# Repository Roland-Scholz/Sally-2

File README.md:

# Sally-2

An ATR8000 (https://www.atarimagazines.com/v3n4/ATR8000.php, http://atariki.krap.pl/index.php/ATR_8000) clone formerly made by SWP
and the Sally 1 by RSD (Rainer Storz Datentechnik)

Inspired by the repair of a Sally 1, which had been found in the attic, the
Atari-Bit-Byter-User-Club (www.abbuc.de) encouraged Marc and me to reproduce this lovely machine in a more compact way, 
though keeping a sort of retro-style.

We used 3 16V8 GALs in order to reduce chip count and replaced the WD1797 floppy-disc-controller by the more compact
WD1772 variant. Caveat: This chip is not designed for HD (500kbit/s) speed used by 3 1/2" and 8"-drives, although most 
can be overclocked to that speed. Only use WD1772PH-02-02 version and at your own risk.
If you can get hold on an AJAX chip used in e.g. ATARI STE, use this one as it is rated for HD and even ED speed (16/32 Mhz).

Build your own device: All required files, components and documentations can be found in the release drawer 
https://github.com/Roland-Scholz/Sally-2/tree/main/release

You also could become an ABBUC member and buy a DIY kit at https://www.abbuc.de
Join the illustrous community and take part in conventions and discussions.

After some testing and debugging, the vRetro VR177x FDC replacement can now be recommended for use with this interface.
See https://www.vretrodesign.com/products/vr177x-wd1770-wd172-vl1772-replacement

# Key features:

- Operates either as standalone CP/M system or versatile ATARI 8-bit interface (up to 4 floppies, Centronics, RS232)
- Z80-CPU at 4Mhz
- 128k static RAM (64k usable)
- 8k EPROM, use any 8 / 16 / 32 / 64k device (burn sally2.hex at $8000)
- WD1772 FDC (or AJAX FDC or VR177x)
- Z80-CTC timer/counter

Additionally we have added:

- 57600 (actually 55.930) baud high speed SIO (Pokey divisor 9, drive responds to the "Get Speed Byte" command '?')
- Track buffer

# Improvements as of November 2026

- Nearly the entire SIO intererface and disk access logic has been rewritten

- Adheres to ATARI SIO standards

- Disk log-in and media-analysis faster and much improved

- More formats, inclusive XF551 track/sector sequence. More or less any valid Percom config is possible

## Typical formats:

| Name | KB    | Sides | Tracks | Sectors | Bytes/Sec | Encoding | Freq      |
| ---- | ----- | ----- | ------ | ------- | --------- | -------- | --------- |
| SD   | 90    | 1     | 40     | 18      | 128       | FM       | 250kbit/s |
| MD   | 130   | 1     | 40     | 26      | 128       | MFM      | 250kbit/s |
| DD1  | 180   | 1     | 40     | 18      | 256       | MFM      | 250kbit/s |
| DD2  | 360   | 1     | 80     | 18      | 256       | MFM      | 250kbit/s |
| DD3  | 360   | 2     | 40     | 18      | 256       | MFM      | 250kbit/s |
| DD4  | 720   | 2     | 80     | 18      | 256       | MFM      | 250kbit/s |
| HD1  | 500,5 | 2     | 77     | 26      | 128       | FM       | 500kbit/s |
| HD2  | 1001  | 2     | 77     | 26      | 256       | MFM      | 500kbit/s |
| HD3  | 1440  | 2     | 80     | 36      | 256       | MFM      | 500kbit/s |
| HD4  | 1440  | 2     | 80     | 18      | 512       | MFM      | 500kbit/s |

# Final product ready as of October 2025

# further progress as of April 2025:

- Marc has completed a new manually routed PCB and 3 supporting PCBs for swicthes and connectors
- ATARI can read/write 3 1/2 HD disks formtted like 8"-disks (26sec x 77 trks x 2 sides = ca. 1MB)
  The challange was to allow for HD even for 300 rpm drives, instead of 360rom used by 8" and 5 1/4" drives.
- A full blown FAT-12 DOS for the ATARI is close to be finished, some more testing and minor additional features required/appreciated
- ABBUC now owns a Bumbu X1-carbon 3D printer, which has immediately been used to dress Sally-2 appropirately.

First try, all-in-one print, label and case

# first attempts

Original Sally 1 repaired (5 ICs were out of order) and tested with a 40Trk single sides drive.

First version of Sally 2 PCB and a case

ATR8000 CP/M running on Sally 1 (todo: Add picture of the Sally CP/M version, which is apart from the messages identical to the ATR8000)

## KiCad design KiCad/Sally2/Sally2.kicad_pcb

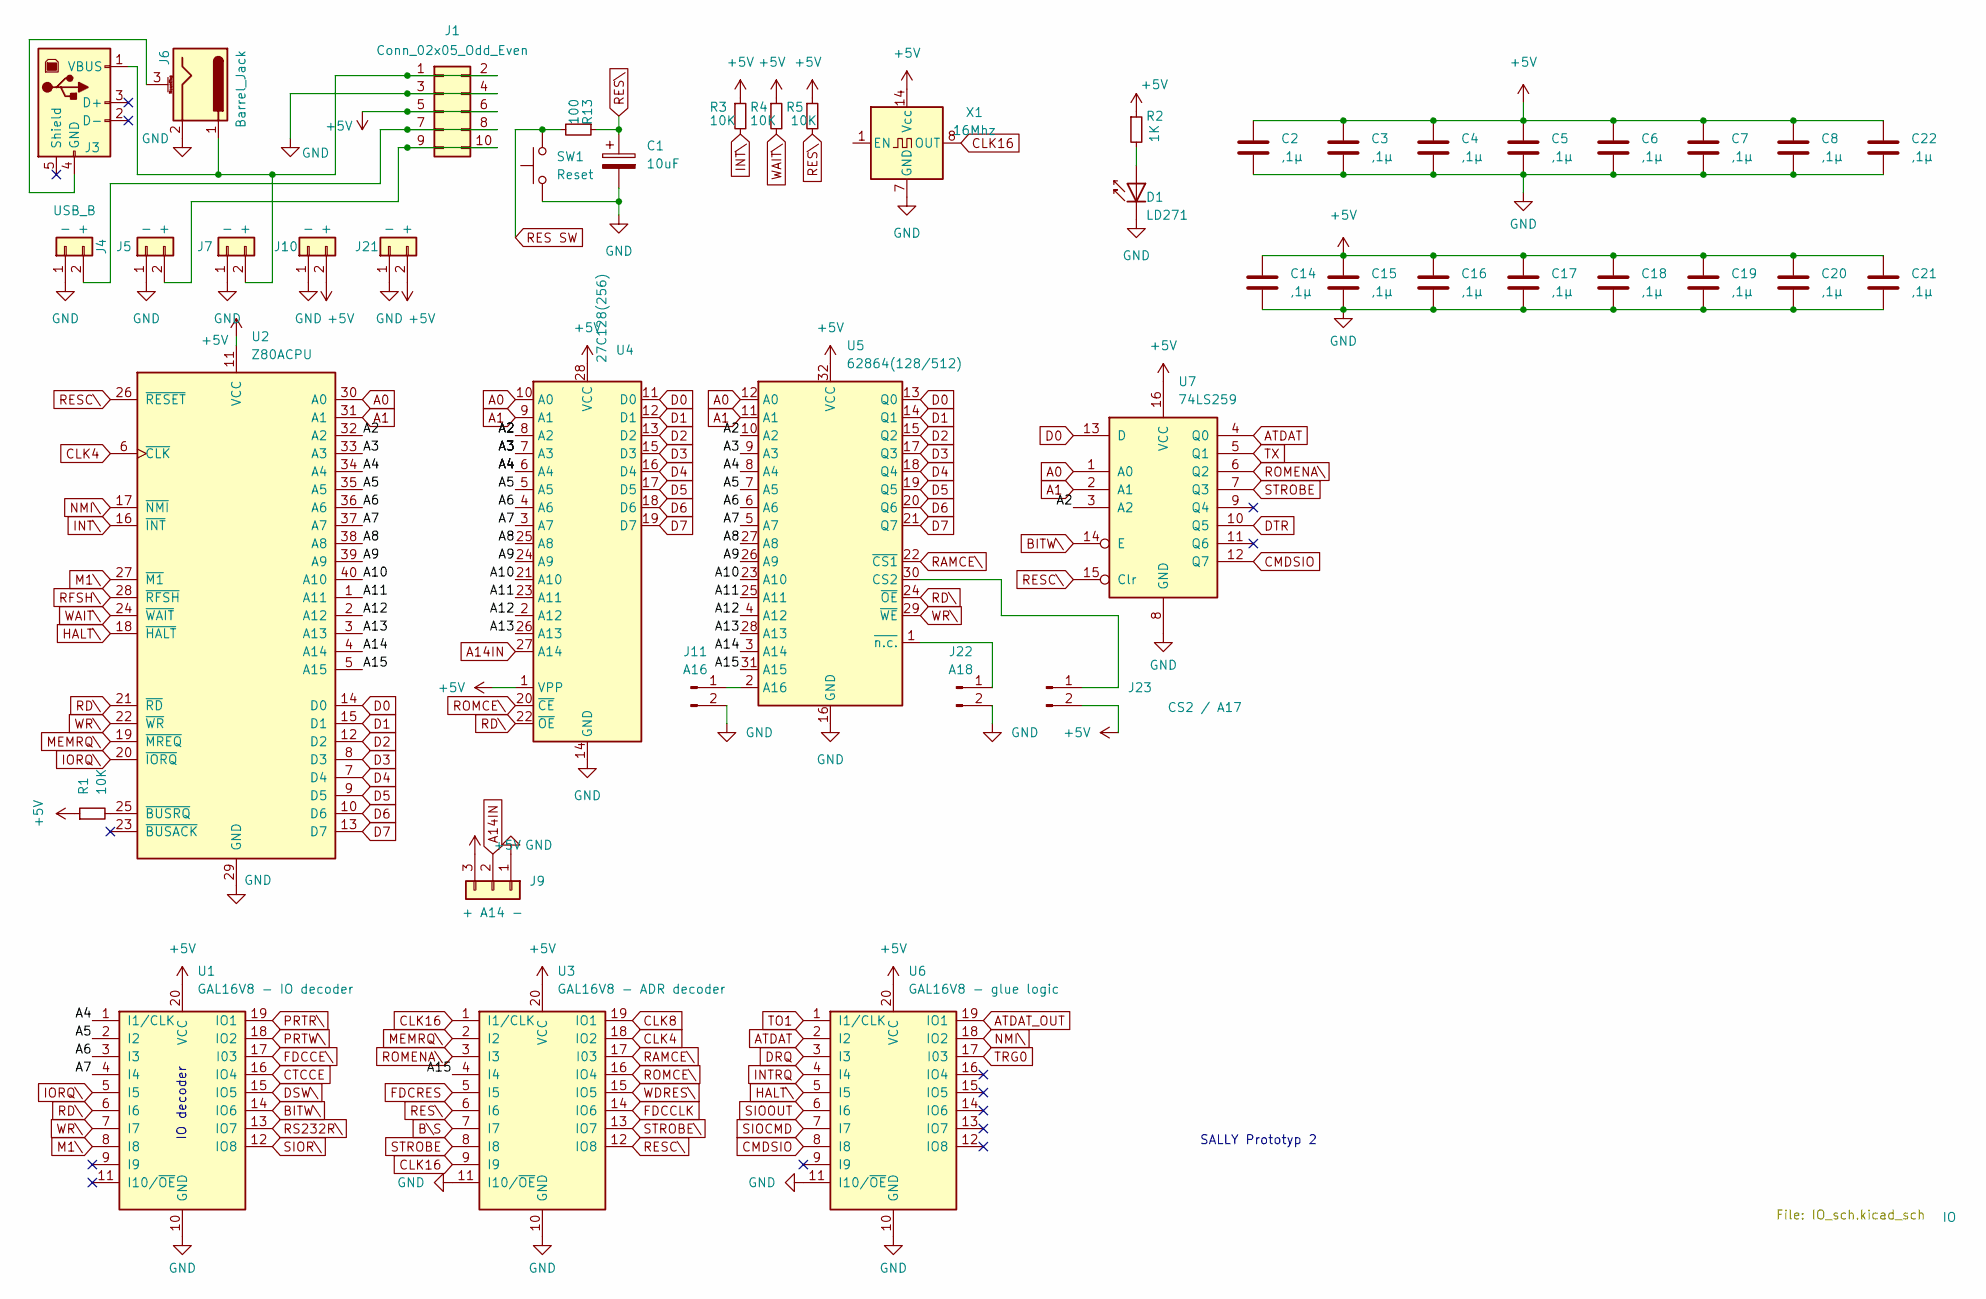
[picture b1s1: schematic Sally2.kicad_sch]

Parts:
C1: 10uF; CP_Radial_D5.0mm_P2.50mm
C2, C3, C4, C5, C6, C7, C8, C14, C15, C16, C17, C18, C19, C20, C21, C22: ,1µ; C_Disc_D5.0mm_W2.5mm_P5.00mm
D1: LD271; LED_D5.0mm_IRGrey
J1: Conn_02x05_Odd_Even; PinHeader_2x05_P2.54mm_Horizontal
J3: USB_B; USB_B_Lumberg_2411_02_Horizontal
J4, J5, J7, J10, J21: - +; BKL_1x2 72510U_P2.5mm_Vertical
J6: Barrel_Jack; BarrelJack_Horizontal
J9: + A14 -; PinHeader_1x03_P2.54mm_Vertical
J11: A16; PinHeader_1x02_P2.54mm_Vertical
J22: A18; PinHeader_1x02_P2.54mm_Vertical
J23: CS2 / A17; PinHeader_1x02_P2.54mm_Vertical
R1, R3, R4, R5: 10K; R_Axial_DIN0207_L6.3mm_D2.5mm_P10.16mm_Horizontal
R2: 1K; R_Axial_DIN0207_L6.3mm_D2.5mm_P10.16mm_Horizontal
R13: 100; R_Axial_DIN0207_L6.3mm_D2.5mm_P10.16mm_Horizontal
SW1: Reset; C_Rect_L7.5mm_W6.5mm_P5.00mm
U1: GAL16V8 - IO decoder; DIP-20_W7.62mm
U2: Z80ACPU; DIP-40_W15.24mm
U3: GAL16V8 - ADR decoder; DIP-20_W7.62mm
U4: 27C128(256); DIP-28_W15.24mm
U5: 62864(128/512); DIP-32_W15.24mm_Socket
U6: GAL16V8 - glue logic; DIP-20_W7.62mm
U7: 74LS259; DIP-16_W7.62mm
X1: 16Mhz; Oscillator_DIP-14

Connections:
+5V: C2.1, C3.1, C4.1, C5.1, C6.1, C7.1, C8.1, C14.1, C15.1, C16.1, C17.1, C18.1, C19.1, C20.1, C21.1, C22.1, J1.5, J1.6, J9.3, J10.2, J21.2, J23.2, R1.1, R2.1, R3.1, R4.1, R5.1, U1.20 (VCC), U2.11 (VCC), U3.20 (VCC), U4.1 (VPP), U4.28 (VCC), U5.32 (VCC), U6.20 (VCC), U7.16 (VCC), X1.14 (Vcc); also elsewhere on the board
/A2: U2.32 (A2), U4.8 (A2), U5.10 (A2), U7.3 (A2)
/A3: U2.33 (A3), U4.7 (A3), U5.9 (A3)
/A4: U1.1 (I1/CLK), U2.34 (A4), U4.6 (A4), U5.8 (A4)
/A5: U1.2 (I2), U2.35 (A5), U4.5 (A5), U5.7 (A5)
/A6: U1.3 (I3), U2.36 (A6), U4.4 (A6), U5.6 (A6)
/A7: U1.4 (I4), U2.37 (A7), U4.3 (A7), U5.5 (A7)
/A8: U2.38 (A8), U4.25 (A8), U5.27 (A8)
/A9: U2.39 (A9), U4.24 (A9), U5.26 (A9)
/A10: U2.40 (A10), U4.21 (A10), U5.23 (A10)
/A11: U2.1 (A11), U4.23 (A11), U5.25 (A11)
/A12: U2.2 (A12), U4.2 (A12), U5.4 (A12)
/A13: U2.3 (A13), U4.26 (A13), U5.28 (A13)
/A14: U2.4 (A14), U5.3 (A14)
/A15: U2.5 (A15), U3.4 (I4), U5.31 (A15)
A0: U2.30 (A0), U4.10 (A0), U5.12 (A0), U7.1 (A0); also elsewhere on the board
A1: U2.31 (A1), U4.9 (A1), U5.11 (A1), U7.2 (A1); also elsewhere on the board
A14IN: J9.2, U4.27 (A14)
ATDAT: U6.2 (I2), U7.4 (Q0)
ATDAT_OUT: U6.19 (IO1); also elsewhere on the board
BITW\: U1.14 (IO6), U7.14 (E)
B\S: U3.7 (I7); also elsewhere on the board
CLK4: U2.6 (~CLK), U3.18 (IO2); also elsewhere on the board
CLK8: U3.19 (IO1)
CLK16: U3.1 (I1/CLK), U3.9 (I9), X1.8 (OUT)
CMDSIO: U6.8 (I8), U7.12 (Q7)
CTCCE: U1.16 (IO4); also elsewhere on the board
D0: U2.14 (D0), U4.11 (D0), U5.13 (Q0), U7.13 (D); also elsewhere on the board
D1: U2.15 (D1), U4.12 (D1), U5.14 (Q1); also elsewhere on the board
D2: U2.12 (D2), U4.13 (D2), U5.15 (Q2); also elsewhere on the board
D3: U2.8 (D3), U4.15 (D3), U5.17 (Q3); also elsewhere on the board
D4: U2.7 (D4), U4.16 (D4), U5.18 (Q4); also elsewhere on the board
D5: U2.9 (D5), U4.17 (D5), U5.19 (Q5); also elsewhere on the board
D6: U2.10 (D6), U4.18 (D6), U5.20 (Q6); also elsewhere on the board
D7: U2.13 (D7), U4.19 (D7), U5.21 (Q7); also elsewhere on the board
DRQ: U6.3 (I3); also elsewhere on the board
DSW\: U1.15 (IO5); also elsewhere on the board
DTR: U7.10 (Q5); also elsewhere on the board
FDCCE\: U1.17 (I03); also elsewhere on the board
FDCCLK: U3.14 (IO6); also elsewhere on the board
FDCRES: U3.5 (I5); also elsewhere on the board
GND: C1.2, C2.2, C3.2, C4.2, C5.2, C6.2, C7.2, C8.2, C14.2, C15.2, C16.2, C17.2, C18.2, C19.2, C20.2, C21.2, C22.2, D1.1 (K), J1.3, J1.4, J4.1, J5.1, J6.2, J7.1, J9.1, J10.1, J11.2, J21.1, J22.2, SW1.1, U1.10 (GND), U2.29 (GND), U3.10 (GND), U3.11 (I10/~OE), U4.14 (GND), U5.16 (GND), U6.10 (GND), U6.11 (I10/~OE), U7.8 (GND), X1.7 (GND); also elsewhere on the board
HALT\: U2.18 (~HALT), U6.5 (I5)
INTRQ: U6.4 (I4); also elsewhere on the board
INT\: R3.2, U2.16 (~INT); also elsewhere on the board
IORQ\: U1.5 (I5), U2.20 (~IORQ); also elsewhere on the board
M1\: U1.8 (I8), U2.27 (~M1); also elsewhere on the board
MEMRQ\: U2.19 (~MREQ), U3.2 (I2)
NMI\: U2.17 (~NMI), U6.18 (IO2)
unnamed: D1.2 (A), R2.2
unnamed: J1.1, J1.2, J3.1 (VBUS), J6.1, J7.2
unnamed: J1.7, J1.8, J4.2
unnamed: J1.9, J1.10, J5.2
unnamed: J3.4 (GND), J6.3 (MountPin)
unnamed: J11.1, U5.2 (A16)
unnamed: J22.1, U5.1 (~n.c.)
unnamed: J23.1, U5.30 (CS2)
unnamed: R1.2, U2.25 (~BUSRQ)
PRTR\: U1.19 (IO1); also elsewhere on the board
PRTW\: U1.18 (IO2); also elsewhere on the board
RAMCE\: U3.17 (I03), U5.22 (~CS1)
RD\: U1.6 (I6), U2.21 (~RD), U4.22 (~OE), U5.24 (~OE); also elsewhere on the board
RES SW: R13.2, SW1.2; also elsewhere on the board
RESC\: U2.26 (~RESET), U3.12 (IO8), U7.15 (Clr); also elsewhere on the board
RES\: C1.1, R5.2, R13.1, U3.6 (I6)
RFSH\: U2.28 (~RFSH)
ROMCE\: U3.16 (IO4), U4.20 (~CE)
ROMENA\: U3.3 (I3), U7.6 (Q2)
RS232R\: U1.13 (IO7); also elsewhere on the board
SIOCMD: U6.7 (I7); also elsewhere on the board
SIOOUT: U6.6 (I6); also elsewhere on the board
SIOR\: U1.12 (IO8); also elsewhere on the board
STROBE: U3.8 (I8), U7.7 (Q3)
STROBE\: U3.13 (IO7); also elsewhere on the board
TO1: U6.1 (I1/CLK); also elsewhere on the board
TRG0: U6.17 (I03); also elsewhere on the board
TX: U7.5 (Q1); also elsewhere on the board
WAIT\: R4.2, U2.24 (~WAIT)
WDRES\: U3.15 (IO5); also elsewhere on the board
WR\: U1.7 (I7), U2.22 (~WR), U5.29 (~WE); also elsewhere on the board

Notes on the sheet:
SALLY Prototyp 2
IO decoder

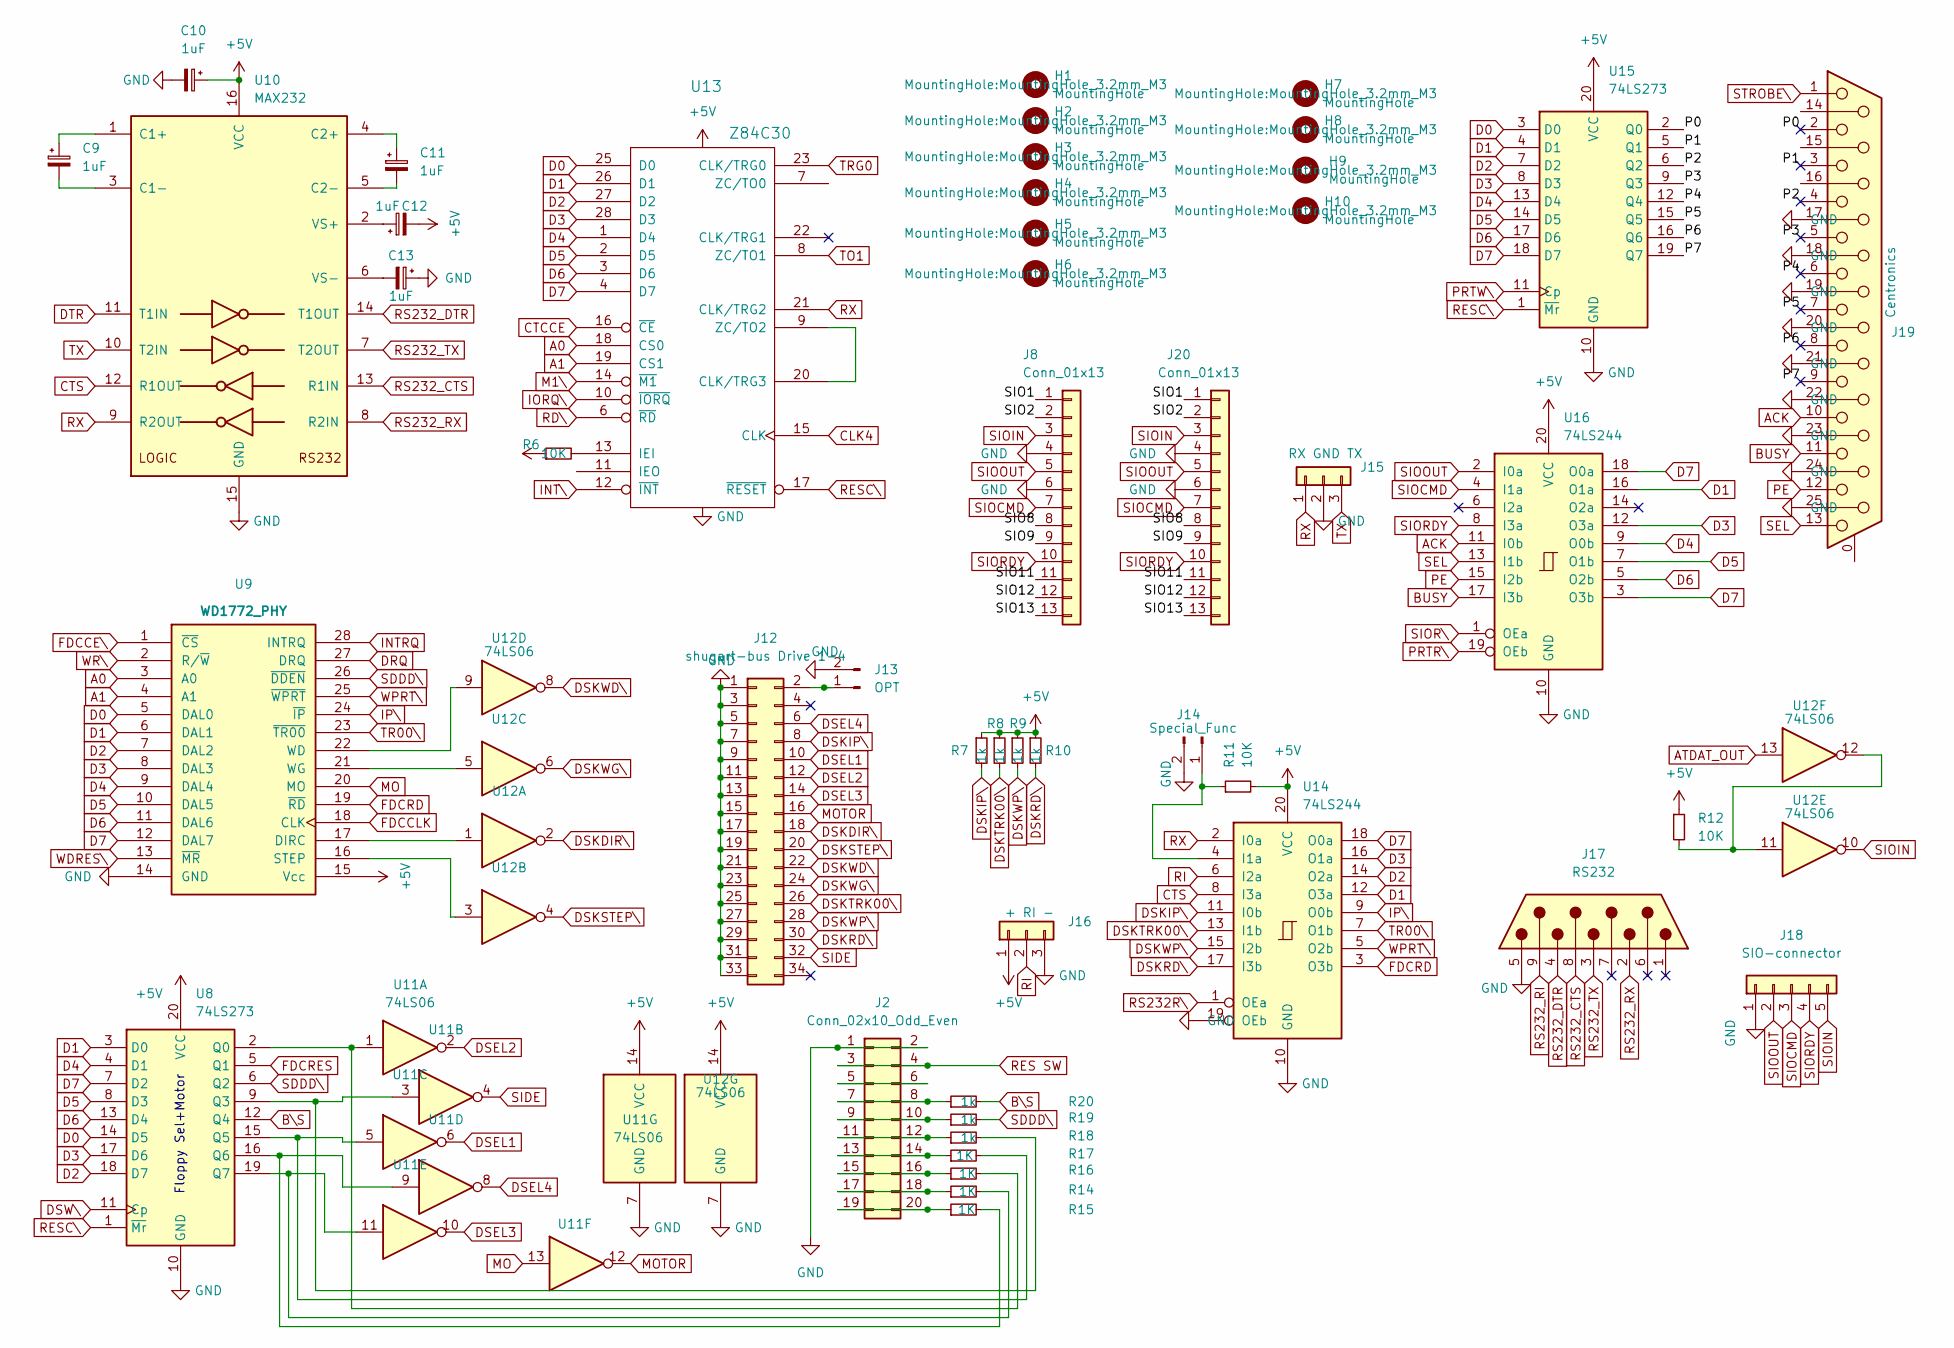
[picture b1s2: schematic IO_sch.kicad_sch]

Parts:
C9, C10, C11, C12, C13: 1uF; CP_Radial_D5.0mm_P2.50mm
H1, H2, H3, H4, H5, H6, H7, H8, H9, H10: MountingHole; MountingHole_3.2mm_M3
J2: Conn_02x10_Odd_Even; PinHeader_2x10_P2.54mm_Horizontal
J8, J20: Conn_01x13; SIO_JACK
J12: shugart-bus Drive 1-4; IDC-Header_2x17_P2.54mm_Vertical
J13: OPT; PinHeader_1x02_P2.54mm_Vertical
J14: Special_Func; PinHeader_1x02_P2.54mm_Vertical
J15: RX GND TX; PinHeader_1x03_P2.54mm_Vertical
J16: + RI -; PinHeader_1x03_P2.54mm_Vertical
J17: RS232; DSUB-9_Male_Horizontal_P2.77x2.84mm_EdgePinOffset9.90mm_Hou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
J18: SIO-connector; PinHeader_1x05_P2.54mm_Vertical
J19: Centronics; DSUB-25_Female_Horizontal_P2.77x2.84mm_EdgePinOffset7.70mm_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
R6, R11, R12: 10K; R_Axial_DIN0207_L6.3mm_D2.5mm_P10.16mm_Horizontal
R7, R8, R9, R10, R18, R19, R20: 1k; R_Axial_DIN0207_L6.3mm_D2.5mm_P10.16mm_Horizontal
R14, R15, R16, R17: 1K; R_Axial_DIN0207_L6.3mm_D2.5mm_P10.16mm_Horizontal
U8, U15: 74LS273; DIP-20_W7.62mm
U9: WD1772_PHY; DIP-28_W15.24mm_LongPads
U10: MAX232; DIP-16_W7.62mm
U11, U12: 74LS06; DIP-14_W7.62mm_Socket
U13: Z84C30; DIP-28_W15.24mm
U14, U16: 74LS244; DIP-20_W7.62mm

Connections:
+5V: C10.1, C12.2, J16.1, R6.1, R7.1, R8.1, R9.1, R10.1, R11.2, R12.1, U8.20 (VCC), U9.15 (Vcc), U10.16 (VCC), U11.14 (VCC), U12.14 (VCC), U13.24 (VCC), U14.20 (VCC), U15.20 (VCC), U16.20 (VCC); also elsewhere on the board
/IO/P0: J19.2, U15.2 (Q0)
/IO/P1: J19.3, U15.5 (Q1)
/IO/P2: J19.4, U15.6 (Q2)
/IO/P3: J19.5, U15.9 (Q3)
/IO/P4: J19.6, U15.12 (Q4)
/IO/P5: J19.7, U15.15 (Q5)
/IO/P6: J19.8, U15.16 (Q6)
/IO/P7: J19.9, U15.19 (Q7)
/IO/SIO1: J8.1, J20.1
/IO/SIO2: J8.2, J20.2
/IO/SIO8: J8.8, J20.8
/IO/SIO9: J8.9, J20.9
/IO/SIO11: J8.11, J20.11
/IO/SIO12: J8.12, J20.12
/IO/SIO13: J8.13, J20.13
A0: U9.3 (A0), U13.18 (CS0); also elsewhere on the board
A1: U9.4 (A1), U13.19 (CS1); also elsewhere on the board
ACK: J19.10, U16.11 (I0b)
ATDAT_OUT: U12.13; also elsewhere on the board
BUSY: J19.11, U16.17 (I3b)
B\S: R20.2, U8.12 (Q4); also elsewhere on the board
CLK4: U13.15 (CLK); also elsewhere on the board
CTCCE: U13.16 (~CE); also elsewhere on the board
CTS: U10.12 (R1OUT), U14.8 (I3a)
D0: U8.14 (D5), U9.5 (DAL0), U13.25 (D0), U15.3 (D0); also elsewhere on the board
D1: U8.3 (D0), U9.6 (DAL1), U13.26 (D1), U14.12 (O3a), U15.4 (D1), U16.16 (O1a); also elsewhere on the board
D2: U8.18 (D7), U9.7 (DAL2), U13.27 (D2), U14.14 (O2a), U15.7 (D2); also elsewhere on the board
D3: U8.17 (D6), U9.8 (DAL3), U13.28 (D3), U14.16 (O1a), U15.8 (D3), U16.12 (O3a); also elsewhere on the board
D4: U8.4 (D1), U9.9 (DAL4), U13.1 (D4), U15.13 (D4), U16.9 (O0b); also elsewhere on the board
D5: U8.8 (D3), U9.10 (DAL5), U13.2 (D5), U15.14 (D5), U16.7 (O1b); also elsewhere on the board
D6: U8.13 (D4), U9.11 (DAL6), U13.3 (D6), U15.17 (D6), U16.5 (O2b); also elsewhere on the board
D7: U8.7 (D2), U9.12 (DAL7), U13.4 (D7), U14.18 (O0a), U15.18 (D7), U16.3 (O3b), U16.18 (O0a); also elsewhere on the board
DRQ: U9.27 (DRQ); also elsewhere on the board
DSEL1: J12.10, U11.6
DSEL2: J12.12, U11.2
DSEL3: J12.14, U11.10
DSEL4: J12.6, U11.8
DSKDIR\: J12.18, U12.2
DSKIP\: J12.8, R7.2, U14.11 (I0b)
DSKRD\: J12.30, R10.2, U14.17 (I3b)
DSKSTEP\: J12.20, U12.4
DSKTRK00\: J12.26, R8.2, U14.13 (I1b)
DSKWD\: J12.22, U12.8
DSKWG\: J12.24, U12.6
DSKWP\: J12.28, R9.2, U14.15 (I2b)
DSW\: U8.11 (Cp); also elsewhere on the board
DTR: U10.11 (T1IN); also elsewhere on the board
FDCCE\: U9.1 (~CS); also elsewhere on the board
FDCCLK: U9.18 (CLK); also elsewhere on the board
FDCRD: U9.19 (~RD), U14.3 (O3b)
FDCRES: U8.5 (Q1); also elsewhere on the board
GND: C10.2, C13.1, J2.1, J2.2, J8.4, J8.6, J12.1, J12.3, J12.5, J12.7, J12.9, J12.11, J12.13, J12.15, J12.17, J12.19, J12.21, J12.23, J12.25, J12.27, J12.29, J12.31, J12.33, J13.2, J14.2, J15.2, J16.3, J17.5, J18.1, J19.17, J19.18, J19.19, J19.20, J19.21, J19.22, J19.23, J19.24, J19.25, J20.4, J20.6, U8.10 (GND), U9.14 (GND), U10.15 (GND), U11.7 (GND), U12.7 (GND), U13.5 (GND), U14.10 (GND), U14.19 (OEb), U15.10 (GND), U16.10 (GND); also elsewhere on the board
INTRQ: U9.28 (INTRQ); also elsewhere on the board
INT\: U13.12 (~INT); also elsewhere on the board
IORQ\: U13.10 (~IORQ); also elsewhere on the board
IP\: U9.24 (~IP), U14.9 (O0b)
M1\: U13.14 (~M1); also elsewhere on the board
MO: U9.20 (MO), U11.13
MOTOR: J12.16, U11.12
unnamed: J2.5, J2.6
unnamed: J2.7, J2.8, R20.1
unnamed: J2.9, J2.10, R19.1
unnamed: J2.11, J2.12, R18.1
unnamed: J2.13, J2.14, R17.1
unnamed: J2.15, J2.16, R16.1
unnamed: J2.17, J2.18, R14.1
unnamed: J2.19, J2.20, R15.1
unnamed: J12.2, J13.1
unnamed: J14.1, R11.1, U14.4 (I1a)
unnamed: R12.2, U12.11, U12.12
unnamed: R16.2, U8.2 (Q0), U11.1
unnamed: R18.2, U8.9 (Q3), U11.3
unnamed: R17.2, U8.15 (Q5), U11.5
unnamed: R15.2, U8.16 (Q6), U11.9
unnamed: R14.2, U8.19 (Q7), U11.11
unnamed: U9.17 (DIRC), U12.1
unnamed: U9.16 (STEP), U12.3
unnamed: U9.22 (WD), U12.9
unnamed: U9.21 (WG), U12.5
unnamed: C9.1, U10.1 (C1+)
unnamed: C9.2, U10.3 (C1-)
unnamed: C11.1, U10.4 (C2+)
unnamed: C11.2, U10.5 (C2-)
unnamed: C12.1, U10.2 (VS+)
unnamed: C13.2, U10.6 (VS-)
unnamed: U13.9 (ZC/TO2), U13.20 (CLK/TRG3)
unnamed: R6.2, U13.13 (IEI)
PE: J19.12, U16.15 (I2b)
PRTR\: U16.19 (OEb); also elsewhere on the board
PRTW\: U15.11 (Cp); also elsewhere on the board
RD\: U13.6 (~RD); also elsewhere on the board
RES SW: J2.3, J2.4; also elsewhere on the board
RESC\: U8.1 (~Mr), U13.17 (~RESET), U15.1 (~Mr); also elsewhere on the board
RI: J16.2, U14.6 (I2a)
RS232R\: U14.1 (OEa); also elsewhere on the board
RS232_CTS: J17.8, U10.13 (R1IN)
RS232_DTR: J17.4, U10.14 (T1OUT)
RS232_RI: J17.9
RS232_RX: J17.2, U10.8 (R2IN)
RS232_TX: J17.3, U10.7 (T2OUT)
RX: J15.1, U10.9 (R2OUT), U13.21 (CLK/TRG2), U14.2 (I0a)
SDDD\: R19.2, U8.6 (Q2), U9.26 (~DDEN)
SEL: J19.13, U16.13 (I1b)
SIDE: J12.32, U11.4
SIOCMD: J8.7, J18.3, J20.7, U16.4 (I1a); also elsewhere on the board
SIOIN: J8.3, J18.5, J20.3, U12.10
SIOOUT: J8.5, J18.2, J20.5, U16.2 (I0a); also elsewhere on the board
SIORDY: J8.10, J18.4, J20.10, U16.8 (I3a)
SIOR\: U16.1 (OEa); also elsewhere on the board
STROBE\: J19.1; also elsewhere on the board
TO1: U13.8 (ZC/TO1); also elsewhere on the board
TR00\: U9.23 (~TR00), U14.7 (O1b)
TRG0: U13.23 (CLK/TRG0); also elsewhere on the board
TX: J15.3, U10.10 (T2IN); also elsewhere on the board
WDRES\: U9.13 (~MR); also elsewhere on the board
WPRT\: U9.25 (~WPRT), U14.5 (O2b)
WR\: U9.2 (R/~W); also elsewhere on the board

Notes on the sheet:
Floppy Sel+Motor

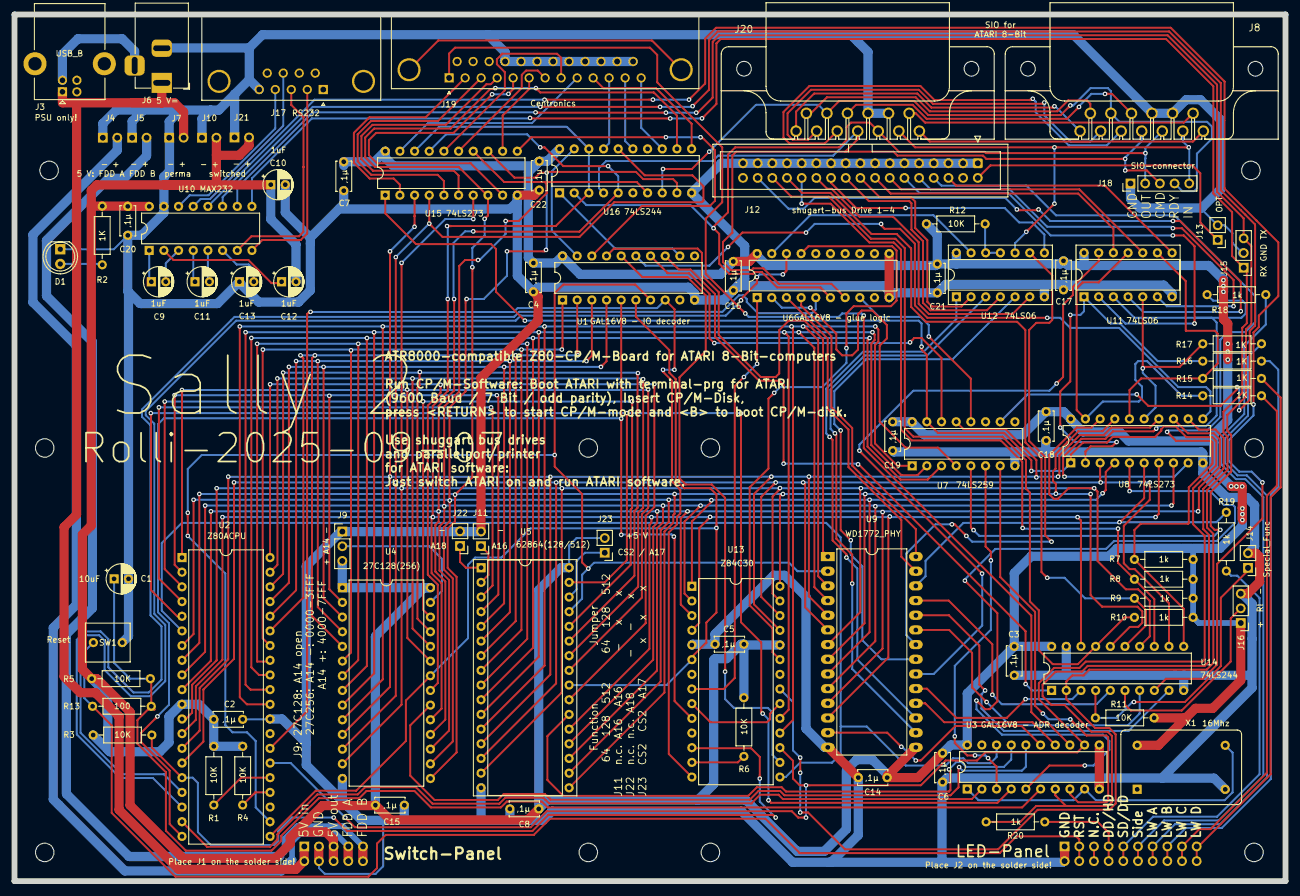
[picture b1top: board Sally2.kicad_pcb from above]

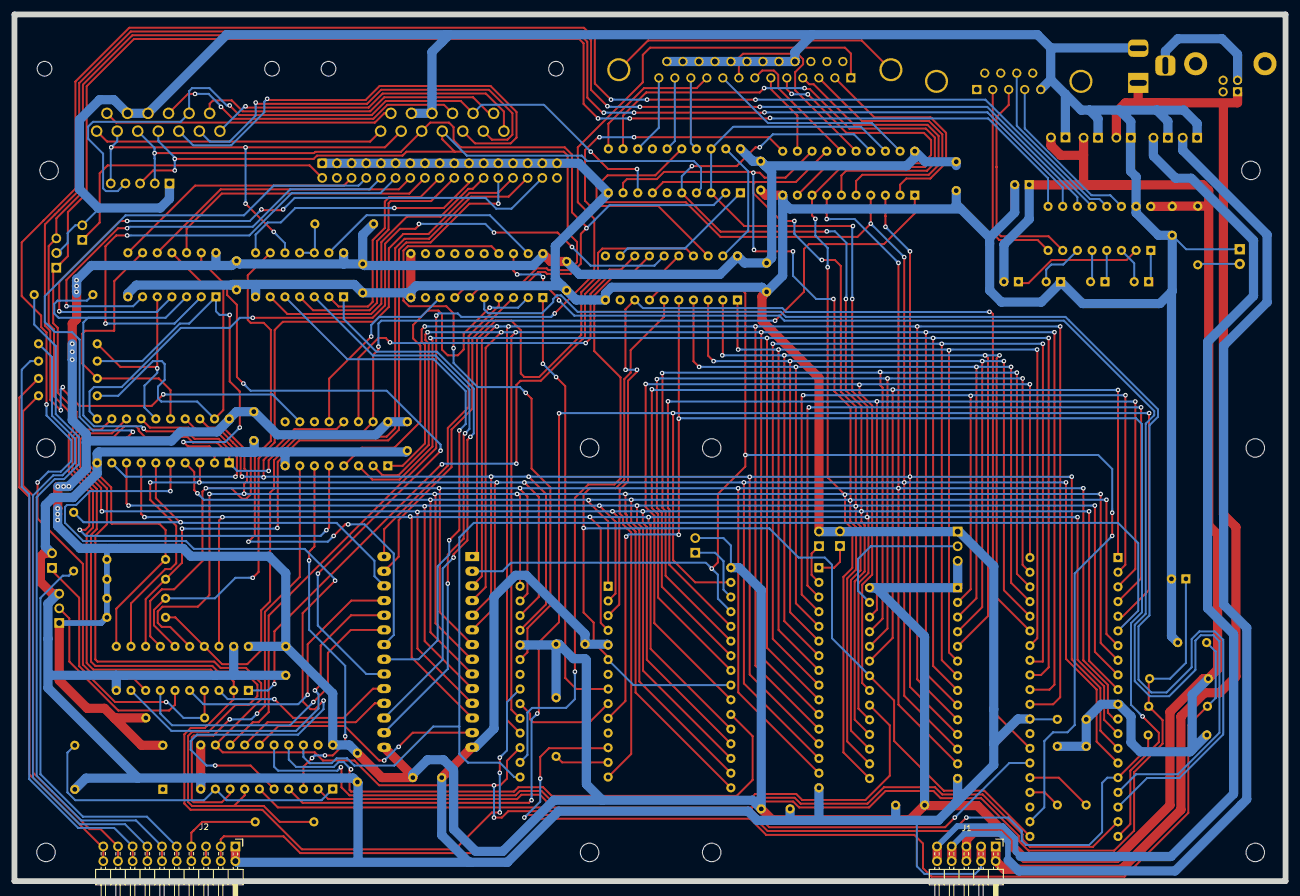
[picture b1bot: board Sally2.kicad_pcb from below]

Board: 2 copper layers, 220.0 x 150.0 mm, 94 parts (2 on the bottom side), 154 nets.

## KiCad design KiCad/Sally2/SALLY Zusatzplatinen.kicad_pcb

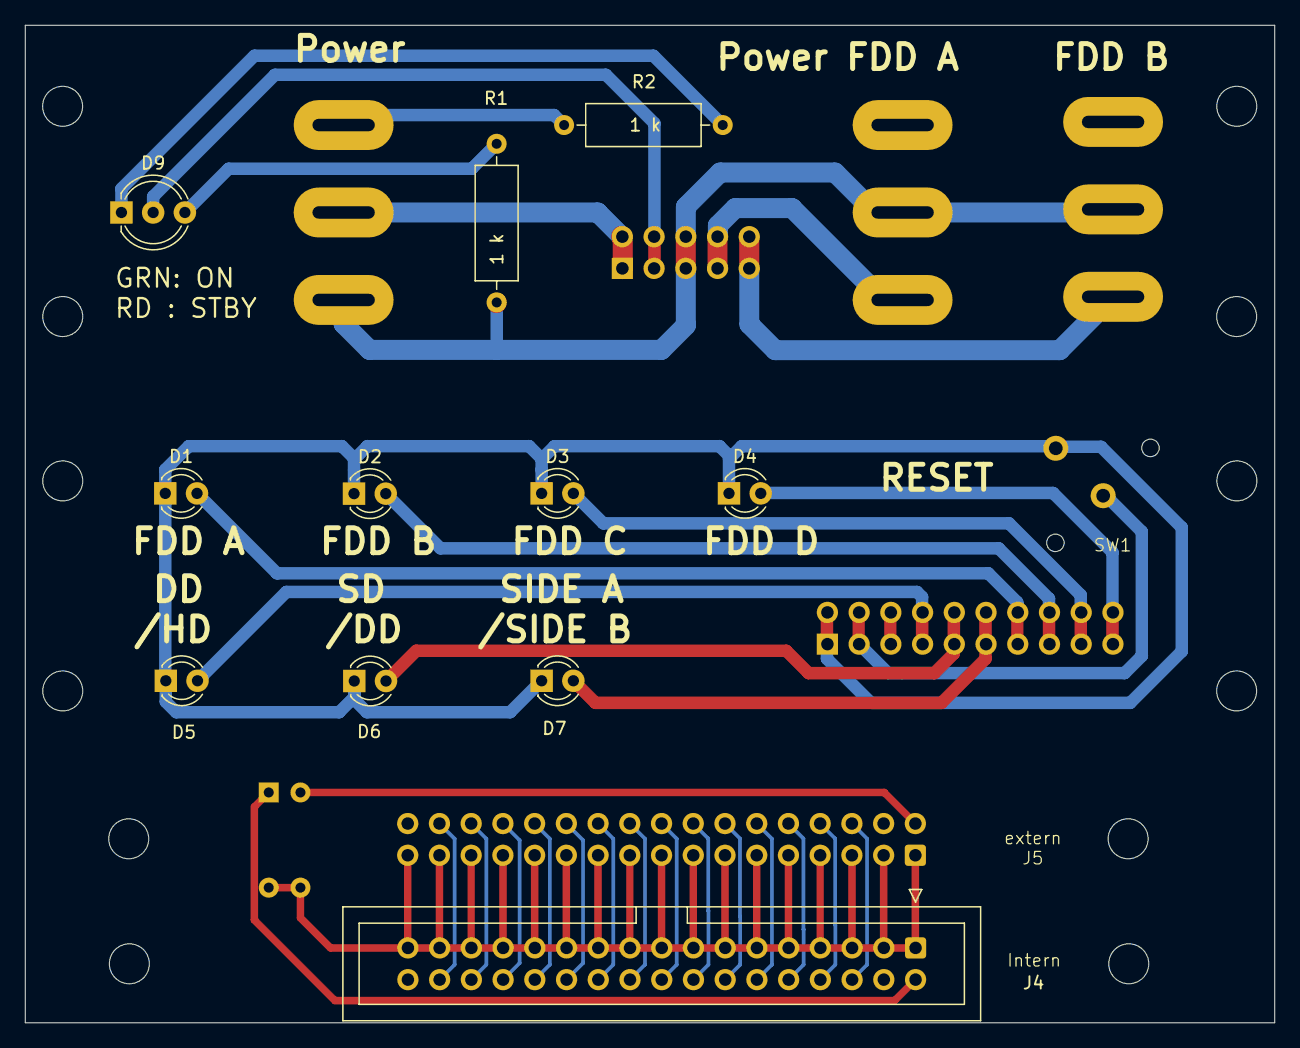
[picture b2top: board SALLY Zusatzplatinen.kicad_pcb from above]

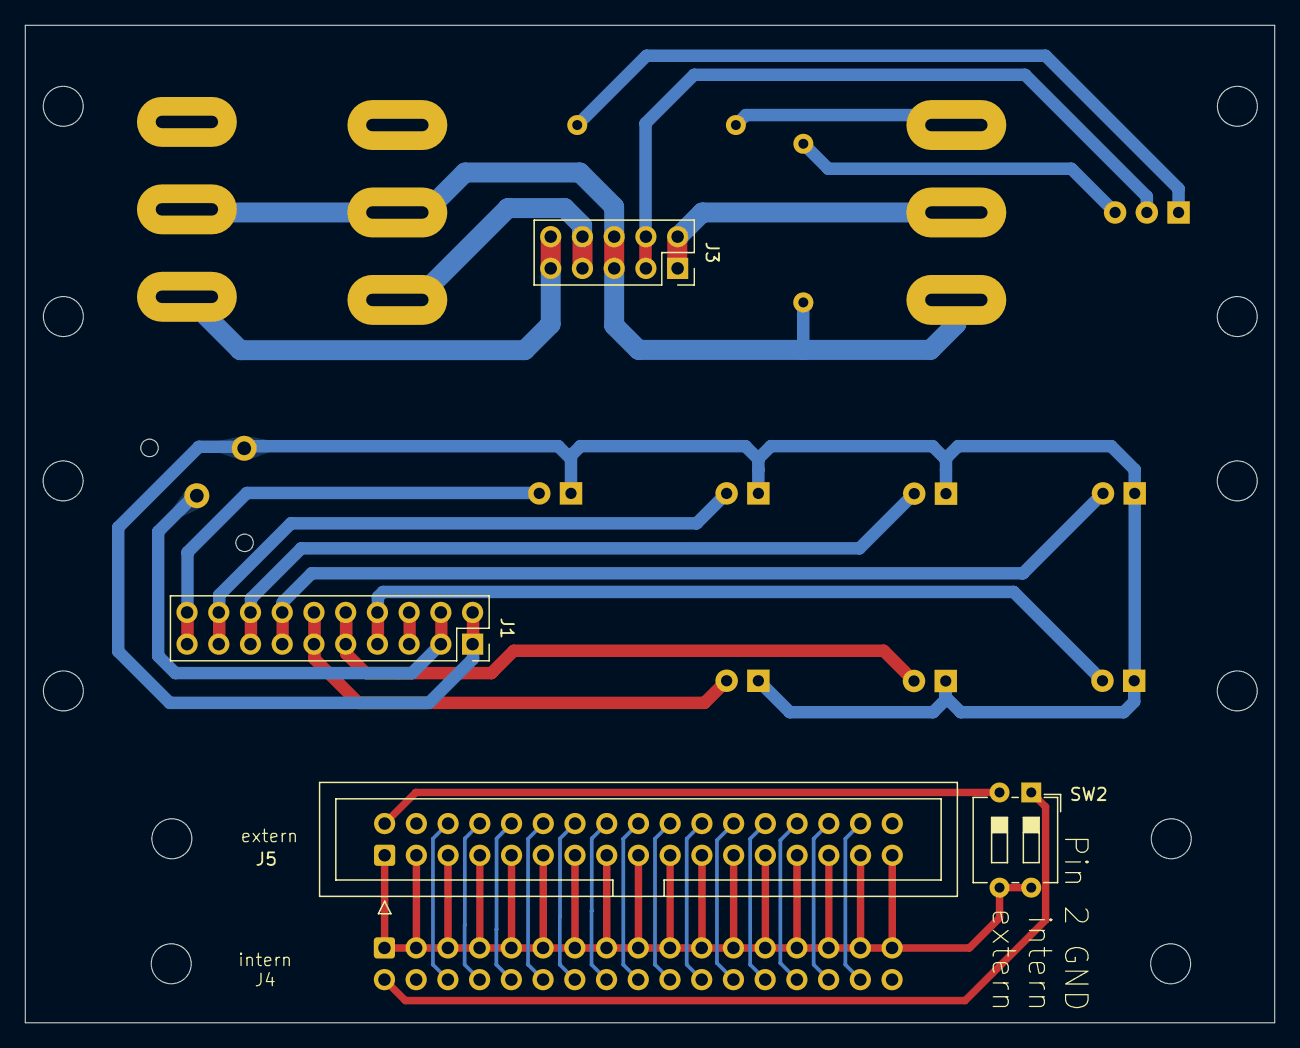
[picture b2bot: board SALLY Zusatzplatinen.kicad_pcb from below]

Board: 2 copper layers, 100.0 x 79.9 mm, 31 parts (4 on the bottom side), 34 nets.

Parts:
D1: LW A; LED_D3.0mm
D2: LW B; LED_D3.0mm
D3: LW C; LED_D3.0mm
D4: LW D; LED_D3.0mm
D5: BS; LED_D3.0mm
D6: DD; LED_D3.0mm
D7: Side; LED_D3.0mm
D9: LED_Dual_AKA; LED_D5.0mm-3
FDD_A1: SW2; MARQUARDT KIPP 1813.1102
FDD_B1: SW3; MARQUARDT KIPP 1813.1102
H1, H2, H3, H4, H5, H6, H7, H8, H9, H10, H11, H12: MountingHole; MountingHole_3.2mm_M3
J1: Conn_02x10_Odd_Even; PinSocket_2x10_P2.54mm_Vertical
J3: Conn_02x05_Odd_Even; PinSocket_2x05_P2.54mm_Vertical
J4: Mainboard; IDC-Header_2x17_P2.54mm_Vertical
J5: FDD extern; IDC-Header_2x17_P2.54mm_Vertical
Power1: SW1; MARQUARDT KIPP 1813.1102
R1, R2: 1 k; R_Axial_DIN0309_L9.0mm_D3.2mm_P12.70mm_Horizontal
SW1: SW_Push; MTG
SW2: SW_DIP_x02; SW_DIP_SPSTx02_Slide_6.7x6.64mm_W7.62mm_P2.54mm_LowProfile

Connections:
unnamed: D1.2 (A), J1.13, J1.14
unnamed: D1.1 (K), D2.1 (K), D3.1 (K), D4.1 (K), D5.1 (K), D6.1 (K), D7.1 (K), J1.1, J1.2, SW1.1
unnamed: D2.2 (A), J1.15, J1.16
unnamed: D3.2 (A), J1.17, J1.18
unnamed: D4.2 (A), J1.19, J1.20
unnamed: D5.2 (A), J1.7, J1.8
unnamed: D6.2 (A), J1.9, J1.10
unnamed: D7.2 (A), J1.11, J1.12
unnamed: D9.1 (A1), R2.1
unnamed: D9.3 (A2), R1.1
unnamed: D9.2 (K), J3.3, J3.4
unnamed: FDD_A1.3 (A), J3.7, J3.8
unnamed: FDD_A1.2 (B), FDD_B1.2 (B), J3.5, J3.6, Power1.3 (A), R1.2
unnamed: FDD_B1.3 (A), J3.9, J3.10
unnamed: J1.3, J1.4, SW1.2
unnamed: J3.1, J3.2, Power1.2 (B)
unnamed: J4.1, J4.3, J4.5, J4.7, J4.9, J4.11, J4.13, J4.15, J4.17, J4.19, J4.21, J4.23, J4.25, J4.27, J4.29, J4.31, J4.33, J5.1, J5.3, J5.5, J5.7, J5.9, J5.11, J5.13, J5.15, J5.17, J5.19, J5.21, J5.23, J5.25, J5.27, J5.29, J5.31, J5.33, SW2.3, SW2.4
unnamed: J4.2, SW2.1
unnamed: J4.6, J5.6
unnamed: J4.8, J5.8
unnamed: J4.10, J5.10
unnamed: J4.12, J5.12
unnamed: J4.14, J5.14
unnamed: J4.16, J5.16
unnamed: J4.18, J5.18
unnamed: J4.20, J5.20
unnamed: J4.22, J5.22
unnamed: J4.24, J5.24
unnamed: J4.26, J5.26
unnamed: J4.28, J5.28
unnamed: J4.30, J5.30
unnamed: J4.32, J5.32
unnamed: J5.2, SW2.2
unnamed: Power1.1 (C), R2.2

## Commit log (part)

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2024-08-04 rollitest
2024-08-04 constants
2024-08-15 WD1772 test
2024-08-15 readsector
2024-08-29 Firmware orig
2024-08-29 Firmware changes
2024-08-30 Atari Write OK
2024-09-07 comments
2024-09-07 format step rate
2024-09-14 hispeed
2024-09-18 kill timer
2024-09-27 trackbuffer read
2024-09-30 Trackbuffer ok
2024-10-10 Release 1.0
    Trackbuffer, HD support, 60000 Baud
2024-10-20 printer buffer length
2024-10-26 tidy-up
2024-10-26 refactor to Sally-2
2024-10-26 KiCad
2024-10-26 readme
2024-10-30 fix RS232 receive (CTC1)
2024-10-30 Sally2
2024-12-06 MSDOS read
2024-12-08 bibliotheken
2024-12-08 IO groß
2024-12-08 IO_sch raus
2024-12-08 IO_sch rein
2024-12-22 MS-DOS write
2025-01-28 LOGSIZE for MSDOS
2025-01-28 sercmd out
2025-03-29 RolliSally 2.Teil
2025-04-12 case 1st try
2025-04-15 Sally-2 case
2025-04-15 front duo-led
2025-04-20 Sally-2 readme case
2025-04-20 typo
2025-04-20 more description
2025-05-01 case update
2025-05-01 fix pic
2025-05-01 black case
2025-05-01 pic cropped
2025-05-08 +pcb pic
2025-05-08 abbuc
2025-05-10 CPM added
2025-05-10 sally-cpm
2025-05-26 case front/back
2025-05-26 chaos/sleepy
2025-05-28 Patricks code merged
2025-05-28 DDINIT for Sally 2 and ATR8000
2025-07-09 WD1772 compile var and formatting
2025-08-20 sallyversion
2025-08-20 Version at end
2025-08-20 no pause
2025-09-01 worked on case
2025-09-05 worked on front (case)
2025-09-20 DINIT3 reverted
2025-09-20 Sally-Logo
2025-10-03 Michael Meincke Ed.
2025-10-28 add more stuff to release drawer
2025-10-28 remove objs from release
2025-10-28 release GAL jed files
2025-10-28 CPM + docs
2025-10-28 autoterm
2025-10-29 WD1772 datasheets
2025-11-14 KiCad merges from Marc
2025-11-14 Autoterm load at $1f00 fixed
2025-11-14 atr80mon.com added
2025-11-19 XL OS Patch
2025-11-20 better way to enable XL OS
2025-11-20 reanabled ATR232.AR0
2025-11-23 write - ACK delay
2025-11-23 COMPLETE with 1ms delay
2025-11-24 sally tools
2025-11-25 revert to 14.10.2025
2025-11-26 read address fixed
2025-12-26 steprate 3ms fixed
2026-01-10 NACK + update firmware @ 08000h
2026-01-12 Inverted SIOOUT & SIOCMD !!
2026-01-16 SIO invert reverted
2026-01-18 ToDo
2026-02-02 sally2rs first working
2026-02-02 Sally2RS Medium Density
2026-02-04 Steprate + 64 Bytes local Diskvars + Diskanalyse Get Percom
2026-02-06 Sally2 CPM diskimage
2026-02-07 receive fast 1 1/2 bit aligned, write protect status
2026-02-15 Pokey Div 9, main.src introduced, code opt
2026-02-17 WIP, do not use
2026-02-17 Trackbuffer working
2026-02-17 4 Sec Motor On
2026-02-18 Write with Verify, Medium Density 26 secs improved
2026-02-18 Write with verify
2026-02-20 optimized disk analysis
2026-02-20 DOS25 Format without Percom
2026-02-20 drive off at getparms
2026-02-22 get SD/MD format right, 26 sec hack for MD Mydos and coderestructured
2026-02-25 Fix 36secs HD readtrk, taken out 26secs hack for MD
2026-02-25 taken out debug log diskwritefn
2026-03-02 GETPARAMS: send 90k Disk Percom
2026-03-04 HD Format with 36 Sectors
2026-03-04 fixed CA-CA list error
2026-03-10 Erhards comments fixed?
2026-03-11 4 sec timer improved
2026-03-15 140 GAP 1, BC fixed
2026-03-16 code opt
2026-03-19 do not use
2026-03-20 untested
2026-03-20 XF551 mode using RI
2026-03-20 sally2.hex working again
2026-03-20 DOS 2-5 format SD, MD without Percom Block
2026-03-20 3ms also for NTRKS = 1
2026-03-23 XF551 support over RI jumper
2026-03-23 512 Byte read
2026-03-23 XF551 mode only if 40 tracks
2026-03-28 XF-Mode format verify 40 tracks only
2026-04-03 Debug mostly off, Format FAT12
2026-04-03 ATR80MON in black and white
2026-04-03 no Debugs
2026-05-10 Sally2 2.0.0
